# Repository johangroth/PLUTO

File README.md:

#PLUTO --- A WDC65C02 based Single Board Computer ---#

###Links to inspirational projects###

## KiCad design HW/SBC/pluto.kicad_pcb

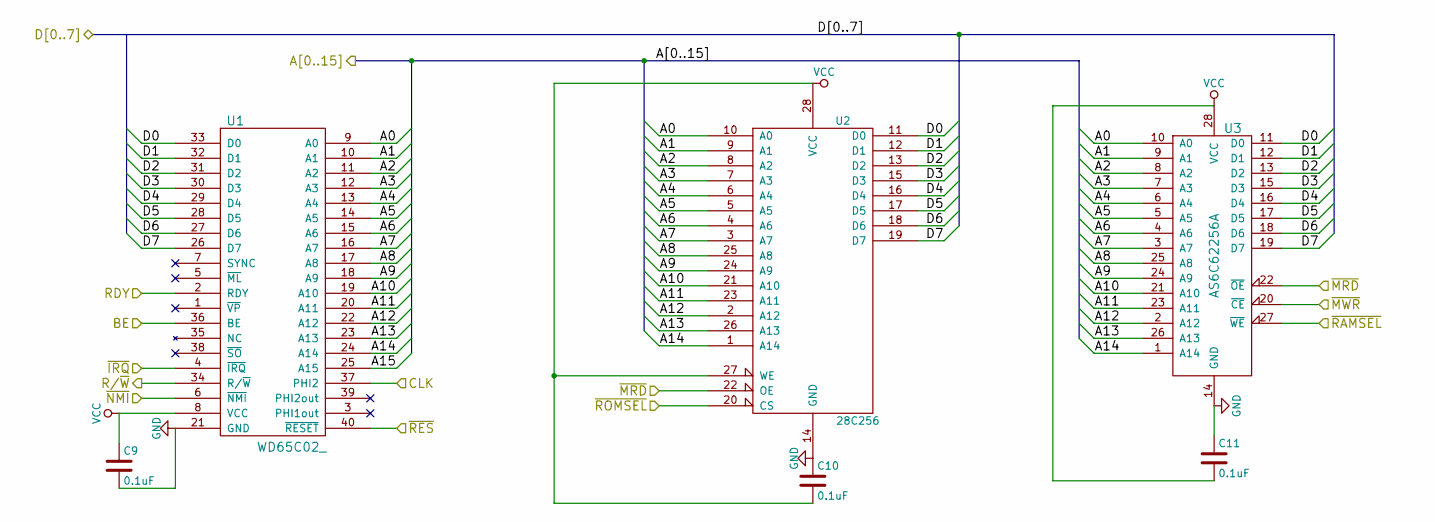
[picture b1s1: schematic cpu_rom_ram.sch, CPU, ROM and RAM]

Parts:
C9, C10, C11: 0.1uF; C_Disc_D3.8mm_W2.6mm_P2.50mm
U1: WD65C02_; DIP-40_W15.24mm_Socket
U2: 28C256; DIP-28_W15.24mm_Socket
U3: AS6C62256A; DIP-28_W15.24mm_Socket

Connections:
/16bit IDE interface/A0: U1.9 (A0), U2.10 (A0), U3.10 (A0); also elsewhere on the board
/16bit IDE interface/A1: U1.10 (A1), U2.9 (A1), U3.9 (A1); also elsewhere on the board
/16bit IDE interface/A2: U1.11 (A2), U2.8 (A2), U3.8 (A2); also elsewhere on the board
/16bit IDE interface/A3: U1.12 (A3), U2.7 (A3), U3.7 (A3); also elsewhere on the board
/16bit IDE interface/CLK: U1.37 (PHI2); also elsewhere on the board
/16bit IDE interface/D0: U1.33 (D0), U2.11 (D0), U3.11 (D0); also elsewhere on the board
/16bit IDE interface/D1: U1.32 (D1), U2.12 (D1), U3.12 (D1); also elsewhere on the board
/16bit IDE interface/D2: U1.31 (D2), U2.13 (D2), U3.13 (D2); also elsewhere on the board
/16bit IDE interface/D3: U1.30 (D3), U2.15 (D3), U3.15 (D3); also elsewhere on the board
/16bit IDE interface/D4: U1.29 (D4), U2.16 (D4), U3.16 (D4); also elsewhere on the board
/16bit IDE interface/D5: U1.28 (D5), U2.17 (D5), U3.17 (D5); also elsewhere on the board
/16bit IDE interface/D6: U1.27 (D6), U2.18 (D6), U3.18 (D6); also elsewhere on the board
/16bit IDE interface/D7: U1.26 (D7), U2.19 (D7), U3.19 (D7); also elsewhere on the board
/16bit IDE interface/~IRQ: U1.4 (~IRQ); also elsewhere on the board
/16bit IDE interface/~MRD: U2.22 (OE), U3.22 (~OE); also elsewhere on the board
/16bit IDE interface/~MWR: U3.20 (~CE); also elsewhere on the board
/16bit IDE interface/~RES: U1.40 (~RESET); also elsewhere on the board
/ACIA and MAX232/R/~W: U1.34 (R/~W); also elsewhere on the board
/Address decoding and support section/A5: U1.14 (A5), U2.5 (A5), U3.5 (A5); also elsewhere on the board
/Address decoding and support section/A6: U1.15 (A6), U2.4 (A6), U3.4 (A6); also elsewhere on the board
/Address decoding and support section/A7: U1.16 (A7), U2.3 (A7), U3.3 (A7); also elsewhere on the board
/Address decoding and support section/A8: U1.17 (A8), U2.25 (A8), U3.25 (A8); also elsewhere on the board
/Address decoding and support section/A9: U1.18 (A9), U2.24 (A9), U3.24 (A9); also elsewhere on the board
/Address decoding and support section/A10: U1.19 (A10), U2.21 (A10), U3.21 (A10); also elsewhere on the board
/Address decoding and support section/A11: U1.20 (A11), U2.23 (A11), U3.23 (A11); also elsewhere on the board
/Address decoding and support section/A12: U1.22 (A12), U2.2 (A12), U3.2 (A12); also elsewhere on the board
/Address decoding and support section/A13: U1.23 (A13), U2.26 (A13), U3.26 (A13); also elsewhere on the board
/Address decoding and support section/A14: U1.24 (A14), U2.1 (A14), U3.1 (A14); also elsewhere on the board
/Address decoding and support section/A15: U1.25 (A15); also elsewhere on the board
/Address decoding and support section/BE: U1.36 (BE); also elsewhere on the board
/Address decoding and support section/RDY: U1.2 (RDY); also elsewhere on the board
/Address decoding and support section/~NMI: U1.6 (~NMI); also elsewhere on the board
/Address decoding and support section/~RAMSEL: U3.27 (~WE); also elsewhere on the board
/Address decoding and support section/~ROMSEL: U2.20 (CS); also elsewhere on the board
/CPU, ROM and RAM/A4: U1.13 (A4), U2.6 (A4), U3.6 (A4); also elsewhere on the board
GND: C9.2, C10.1, C11.1, U1.21 (GND), U2.14 (GND), U3.14 (GND); also elsewhere on the board
VCC: C9.1, C10.2, C11.2, U1.8 (VCC), U2.27 (WE), U2.28 (VCC), U3.28 (VCC); also elsewhere on the board

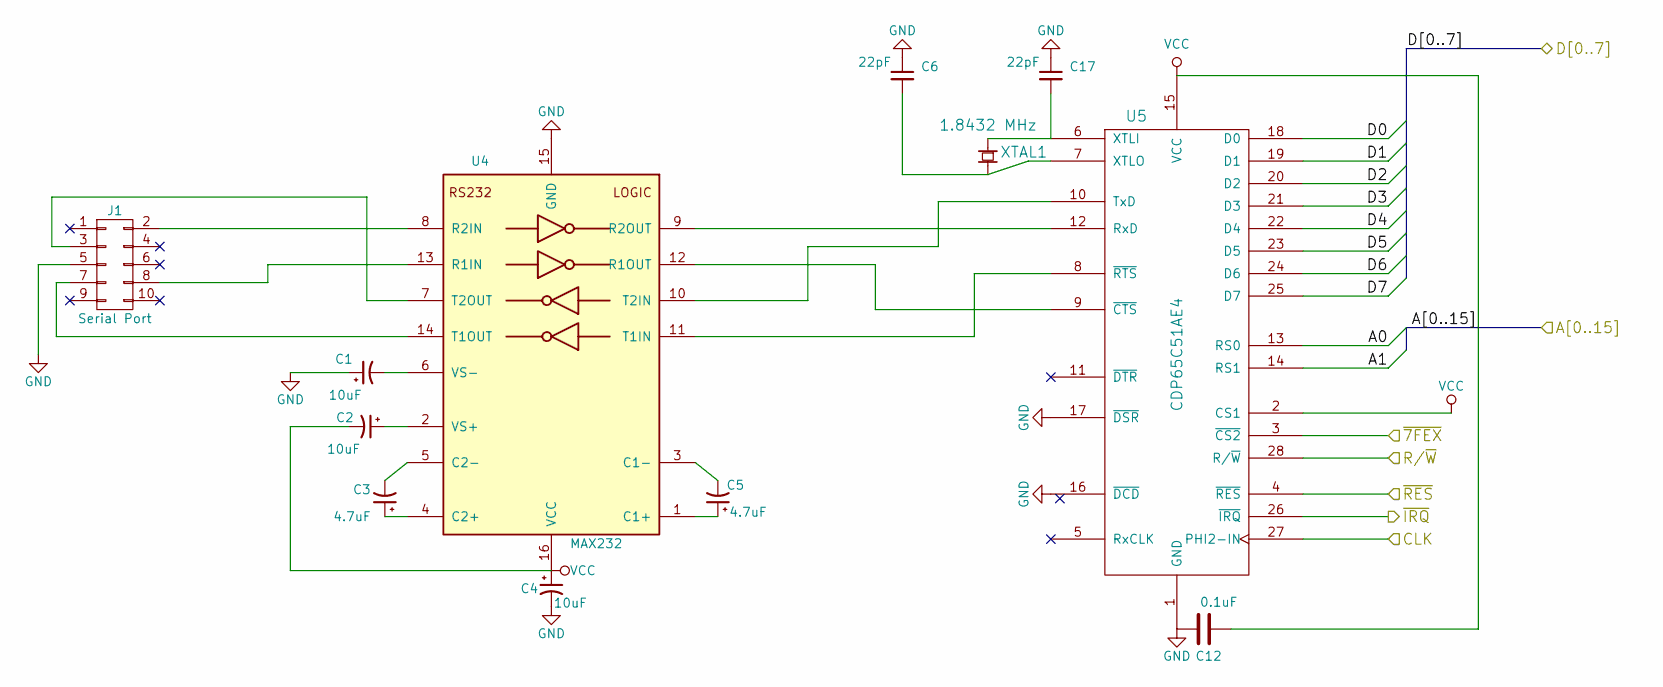
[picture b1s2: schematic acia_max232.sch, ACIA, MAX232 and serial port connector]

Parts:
C1, C2, C4: 10uF; CP_Radial_D5.0mm_P2.50mm
C3, C5: 4.7uF; CP_Radial_D5.0mm_P2.50mm
C6, C17: 22pF; C_Disc_D3.8mm_W2.6mm_P2.50mm
C12: 0.1uF; C_Disc_D3.8mm_W2.6mm_P2.50mm
J1: Serial Port; IDC_Header_Straight_10pins
U4: MAX232; DIP-16_W7.62mm_Socket
U5: CDP65C51AE4; DIP-28_W15.24mm_Socket
XTAL1: 1.8432 MHz; Resonator-2pin_w10.0mm_h5.0mm

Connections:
/16bit IDE interface/A0: U5.13 (RS0); also elsewhere on the board
/16bit IDE interface/A1: U5.14 (RS1); also elsewhere on the board
/16bit IDE interface/CLK: U5.27 (PHI2-IN); also elsewhere on the board
/16bit IDE interface/D0: U5.18 (D0); also elsewhere on the board
/16bit IDE interface/D1: U5.19 (D1); also elsewhere on the board
/16bit IDE interface/D2: U5.20 (D2); also elsewhere on the board
/16bit IDE interface/D3: U5.21 (D3); also elsewhere on the board
/16bit IDE interface/D4: U5.22 (D4); also elsewhere on the board
/16bit IDE interface/D5: U5.23 (D5); also elsewhere on the board
/16bit IDE interface/D6: U5.24 (D6); also elsewhere on the board
/16bit IDE interface/D7: U5.25 (D7); also elsewhere on the board
/16bit IDE interface/~IRQ: U5.26 (~IRQ); also elsewhere on the board
/16bit IDE interface/~RES: U5.4 (~RES); also elsewhere on the board
/ACIA and MAX232/R/~W: U5.28 (R/~W); also elsewhere on the board
/ACIA and MAX232/~7FEX: U5.3 (~CS2); also elsewhere on the board
GND: C1.1, C4.2, C6.1, C12.2, C17.1, J1.5, U4.15 (GND), U5.1 (GND), U5.16 (~DCD), U5.17 (~DSR); also elsewhere on the board
unnamed: C1.2, U4.6 (VS-)
unnamed: C2.1, U4.2 (VS+)
unnamed: C3.1, U4.4 (C2+)
unnamed: C3.2, U4.5 (C2-)
unnamed: C5.1, U4.1 (C1+)
unnamed: C5.2, U4.3 (C1-)
unnamed: C6.2, U5.7 (XTLO), XTAL1.2
unnamed: C17.2, U5.6 (XTLI), XTAL1.1
unnamed: J1.2, U4.8 (R2IN)
unnamed: J1.3, U4.7 (T2OUT)
unnamed: J1.7, U4.14 (T1OUT)
unnamed: J1.8, U4.13 (R1IN)
unnamed: U4.9 (R2OUT), U5.12 (RxD)
unnamed: U4.10 (T2IN), U5.10 (TxD)
unnamed: U4.11 (T1IN), U5.8 (~RTS)
unnamed: U4.12 (R1OUT), U5.9 (~CTS)
VCC: C2.2, C4.1, C12.1, U4.16 (VCC), U5.2 (CS1), U5.15 (VCC); also elsewhere on the board

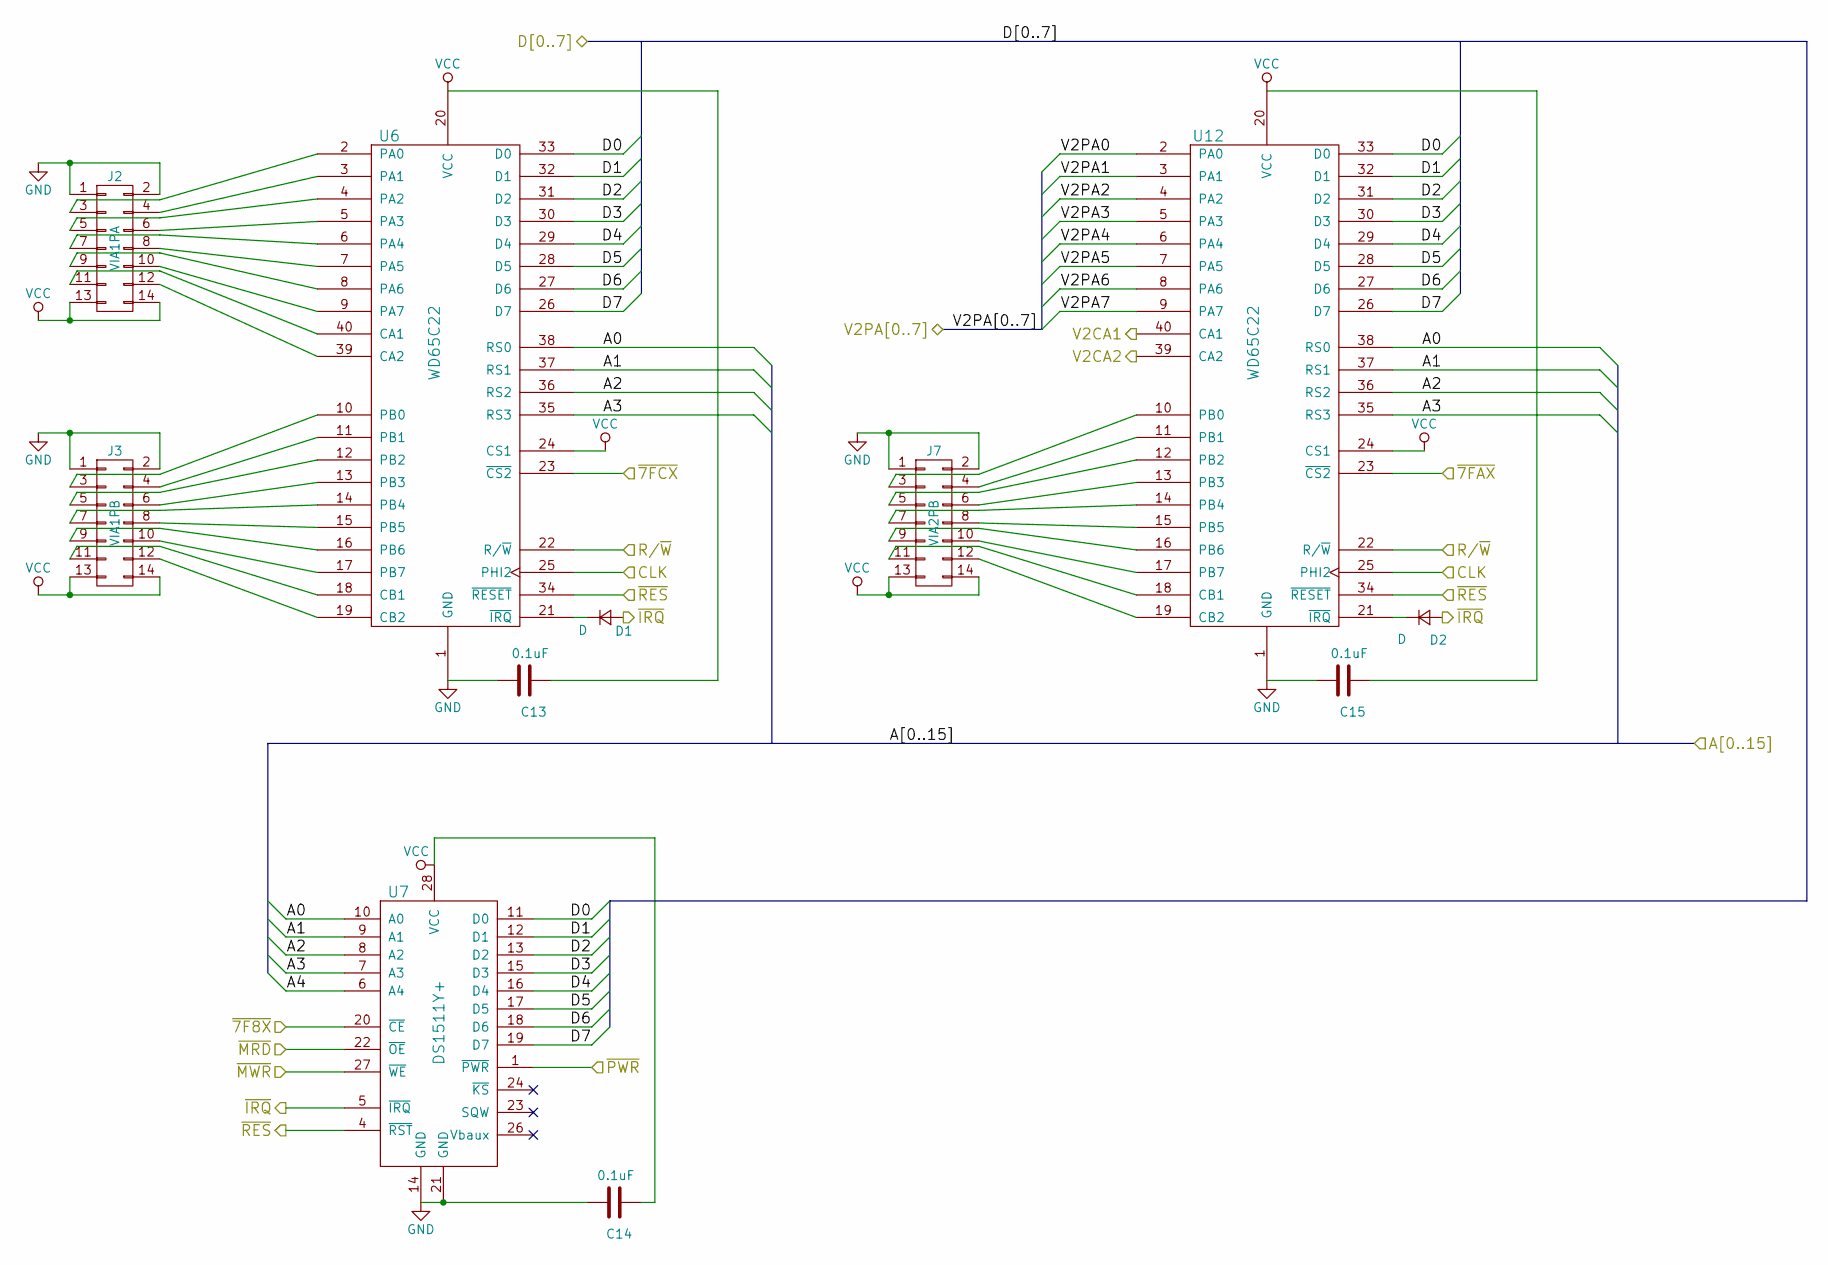
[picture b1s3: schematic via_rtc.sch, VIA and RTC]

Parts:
C13, C14, C15: 0.1uF; C_Disc_D3.8mm_W2.6mm_P2.50mm
D1, D2: D; D_DO-35_SOD27_P7.62mm_Horizontal
J2: VIA1PA; IDC_Header_Straight_14pins
J3: VIA1PB; IDC_Header_Straight_14pins
J7: VIA2PB; IDC_Header_Straight_14pins
U6, U12: WD65C22; DIP-40_W15.24mm_Socket
U7: DS1511Y+; DIP-28_W15.24mm_Socket

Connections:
/16bit IDE interface/A0: U6.38 (RS0), U7.10 (A0), U12.38 (RS0); also elsewhere on the board
/16bit IDE interface/A1: U6.37 (RS1), U7.9 (A1), U12.37 (RS1); also elsewhere on the board
/16bit IDE interface/A2: U6.36 (RS2), U7.8 (A2), U12.36 (RS2); also elsewhere on the board
/16bit IDE interface/A3: U6.35 (RS3), U7.7 (A3), U12.35 (RS3); also elsewhere on the board
/16bit IDE interface/CLK: U6.25 (PHI2), U12.25 (PHI2); also elsewhere on the board
/16bit IDE interface/D0: U6.33 (D0), U7.11 (D0), U12.33 (D0); also elsewhere on the board
/16bit IDE interface/D1: U6.32 (D1), U7.12 (D1), U12.32 (D1); also elsewhere on the board
/16bit IDE interface/D2: U6.31 (D2), U7.13 (D2), U12.31 (D2); also elsewhere on the board
/16bit IDE interface/D3: U6.30 (D3), U7.15 (D3), U12.30 (D3); also elsewhere on the board
/16bit IDE interface/D4: U6.29 (D4), U7.16 (D4), U12.29 (D4); also elsewhere on the board
/16bit IDE interface/D5: U6.28 (D5), U7.17 (D5), U12.28 (D5); also elsewhere on the board
/16bit IDE interface/D6: U6.27 (D6), U7.18 (D6), U12.27 (D6); also elsewhere on the board
/16bit IDE interface/D7: U6.26 (D7), U7.19 (D7), U12.26 (D7); also elsewhere on the board
/16bit IDE interface/~IRQ: D1.2 (A), D2.2 (A), U7.5 (~IRQ); also elsewhere on the board
/16bit IDE interface/~MRD: U7.22 (~OE); also elsewhere on the board
/16bit IDE interface/~MWR: U7.27 (~WE); also elsewhere on the board
/16bit IDE interface/~RES: U6.34 (~RESET), U7.4 (~RST), U12.34 (~RESET); also elsewhere on the board
/ACIA and MAX232/R/~W: U6.22 (R/~W), U12.22 (R/~W); also elsewhere on the board
/Address decoding and support section/~7F8X: U7.20 (~CE); also elsewhere on the board
/Address decoding and support section/~7FAX: U12.23 (~CS2); also elsewhere on the board
/Address decoding and support section/~7FCX: U6.23 (~CS2); also elsewhere on the board
/Address decoding and support section/~PWR: U7.1 (~PWR); also elsewhere on the board
/Audio/V2CA1: U12.40 (CA1); also elsewhere on the board
/Audio/V2CA2: U12.39 (CA2); also elsewhere on the board
/Audio/V2PA0: U12.2 (PA0); also elsewhere on the board
/Audio/V2PA1: U12.3 (PA1); also elsewhere on the board
/Audio/V2PA2: U12.4 (PA2); also elsewhere on the board
/Audio/V2PA3: U12.5 (PA3); also elsewhere on the board
/Audio/V2PA4: U12.6 (PA4); also elsewhere on the board
/Audio/V2PA5: U12.7 (PA5); also elsewhere on the board
/Audio/V2PA6: U12.8 (PA6); also elsewhere on the board
/Audio/V2PA7: U12.9 (PA7); also elsewhere on the board
/CPU, ROM and RAM/A4: U7.6 (A4); also elsewhere on the board
GND: C13.2, C14.2, C15.2, J2.1, J2.2, J3.1, J3.2, J7.1, J7.2, U6.1 (GND), U7.14 (GND), U7.21 (GND), U12.1 (GND); also elsewhere on the board
unnamed: D1.1 (K), U6.21 (~IRQ)
unnamed: D2.1 (K), U12.21 (~IRQ)
unnamed: J2.3, U6.2 (PA0)
unnamed: J2.4, U6.3 (PA1)
unnamed: J2.5, U6.4 (PA2)
unnamed: J2.6, U6.5 (PA3)
unnamed: J2.7, U6.6 (PA4)
unnamed: J2.8, U6.7 (PA5)
unnamed: J2.9, U6.8 (PA6)
unnamed: J2.10, U6.9 (PA7)
unnamed: J2.11, U6.40 (CA1)
unnamed: J2.12, U6.39 (CA2)
unnamed: J3.3, U6.10 (PB0)
unnamed: J3.4, U6.11 (PB1)
unnamed: J3.5, U6.12 (PB2)
unnamed: J3.6, U6.13 (PB3)
unnamed: J3.7, U6.14 (PB4)
unnamed: J3.8, U6.15 (PB5)
unnamed: J3.9, U6.16 (PB6)
unnamed: J3.10, U6.17 (PB7)
unnamed: J3.11, U6.18 (CB1)
unnamed: J3.12, U6.19 (CB2)
unnamed: J7.3, U12.10 (PB0)
unnamed: J7.4, U12.11 (PB1)
unnamed: J7.5, U12.12 (PB2)
unnamed: J7.6, U12.13 (PB3)
unnamed: J7.7, U12.14 (PB4)
unnamed: J7.8, U12.15 (PB5)
unnamed: J7.9, U12.16 (PB6)
unnamed: J7.10, U12.17 (PB7)
unnamed: J7.11, U12.18 (CB1)
unnamed: J7.12, U12.19 (CB2)
VCC: C13.1, C14.1, C15.1, J2.13, J2.14, J3.13, J3.14, J7.13, J7.14, U6.20 (VCC), U6.24 (CS1), U7.28 (VCC), U12.20 (VCC), U12.24 (CS1); also elsewhere on the board

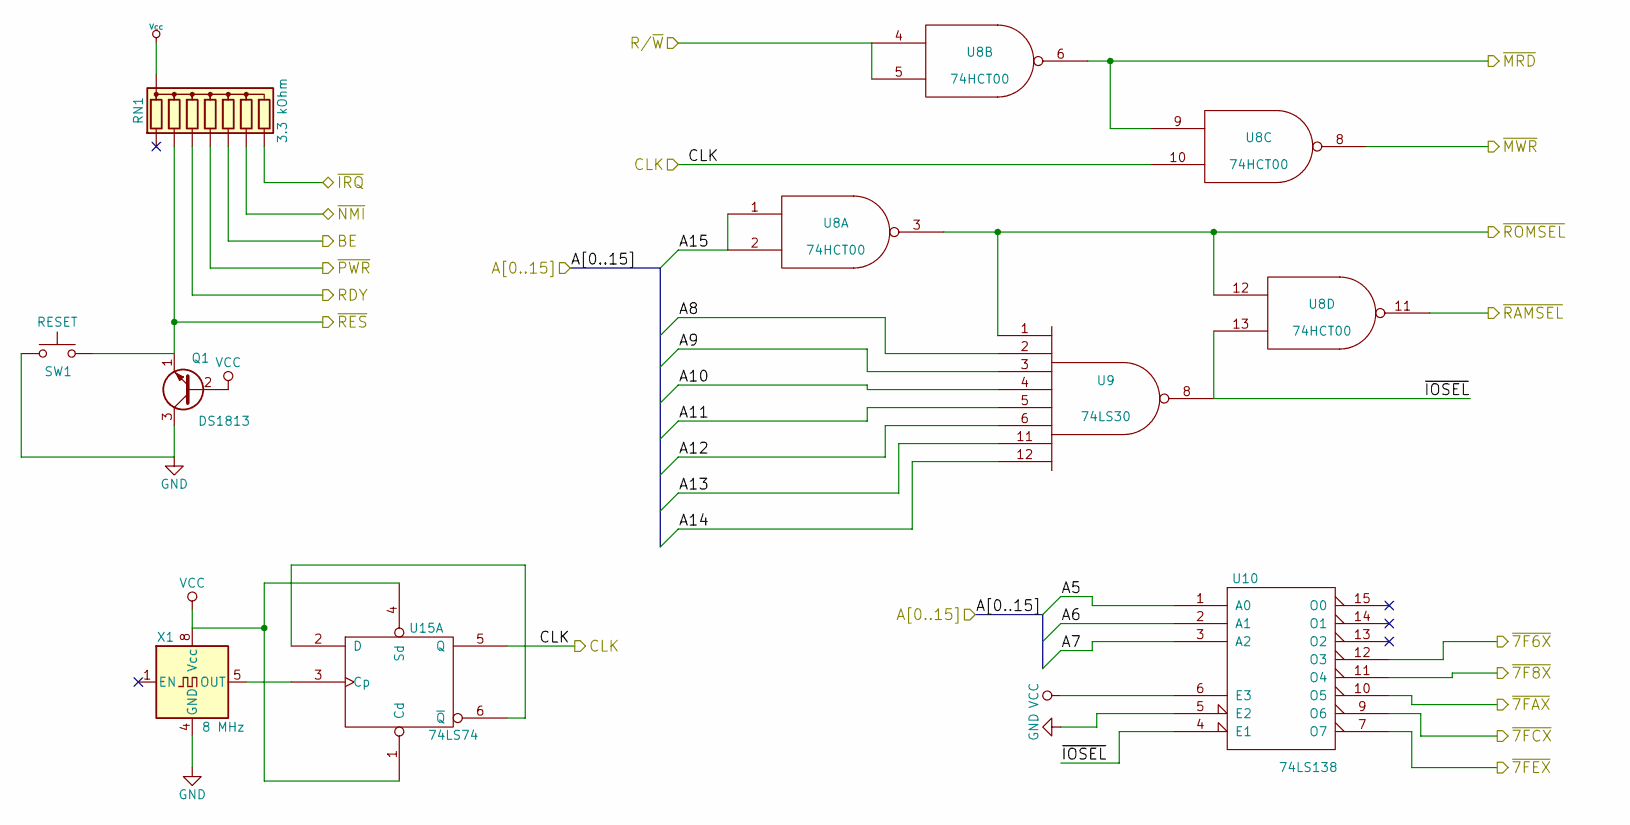
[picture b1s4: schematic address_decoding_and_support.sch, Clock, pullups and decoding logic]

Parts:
Q1: DS1813; TO-92_Inline_Narrow_Oval
RN1: 3.3 kOhm; Pin_Header_Straight_1x08_Pitch2.54mm
SW1: RESET; SW_PUSH_6mm_h4.3mm
U8: 74HCT00; DIP-14_W7.62mm_Socket
U9: 74LS30; DIP-14_W7.62mm_Socket
U10: 74LS138; DIP-16_W7.62mm_Socket
U15: 74LS74; DIP-14_W7.62mm_Socket
X1: 8 MHz; DIP-8_W7.62mm_Socket

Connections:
/16bit IDE interface/CLK: U8.10, U15.5 (Q); also elsewhere on the board
/16bit IDE interface/~7F6X: U10.12 (O3); also elsewhere on the board
/16bit IDE interface/~IRQ: RN1.8 (R7); also elsewhere on the board
/16bit IDE interface/~MRD: U8.6, U8.9; also elsewhere on the board
/16bit IDE interface/~MWR: U8.8; also elsewhere on the board
/16bit IDE interface/~RES: Q1.1 (E), RN1.3 (R2), SW1.2; also elsewhere on the board
/ACIA and MAX232/R/~W: U8.4, U8.5; also elsewhere on the board
/ACIA and MAX232/~7FEX: U10.7 (O7); also elsewhere on the board
/Address decoding and support section/A5: U10.1 (A0); also elsewhere on the board
/Address decoding and support section/A6: U10.2 (A1); also elsewhere on the board
/Address decoding and support section/A7: U10.3 (A2); also elsewhere on the board
/Address decoding and support section/A8: U9.2; also elsewhere on the board
/Address decoding and support section/A9: U9.3; also elsewhere on the board
/Address decoding and support section/A10: U9.4; also elsewhere on the board
/Address decoding and support section/A11: U9.5; also elsewhere on the board
/Address decoding and support section/A12: U9.6; also elsewhere on the board
/Address decoding and support section/A13: U9.11; also elsewhere on the board
/Address decoding and support section/A14: U9.12; also elsewhere on the board
/Address decoding and support section/A15: U8.1, U8.2; also elsewhere on the board
/Address decoding and support section/BE: RN1.6 (R5); also elsewhere on the board
/Address decoding and support section/RDY: RN1.4 (R3); also elsewhere on the board
/Address decoding and support section/~7F8X: U10.11 (O4); also elsewhere on the board
/Address decoding and support section/~7FAX: U10.10 (O5); also elsewhere on the board
/Address decoding and support section/~7FCX: U10.9 (O6); also elsewhere on the board
/Address decoding and support section/~IOSEL: U8.13, U9.8, U10.4 (E1)
/Address decoding and support section/~NMI: RN1.7 (R6); also elsewhere on the board
/Address decoding and support section/~PWR: RN1.5 (R4); also elsewhere on the board
/Address decoding and support section/~RAMSEL: U8.11; also elsewhere on the board
/Address decoding and support section/~ROMSEL: U8.3, U8.12, U9.1; also elsewhere on the board
GND: Q1.3 (C), SW1.1, U8.7 (GND), U9.7 (GND), U10.5 (E2), U10.8 (GND), U15.7 (GND), X1.4 (GND); also elsewhere on the board
unnamed: U15.2 (D), U15.6 (~Q)
unnamed: U15.3 (Cp), X1.5 (OUT)
VCC: Q1.2 (B), RN1.1 (common), U8.14 (VCC), U9.14 (VCC), U10.6 (E3), U10.16 (VCC), U15.1 (Cd), U15.4 (Sd), U15.14 (VCC), X1.8 (Vcc); also elsewhere on the board

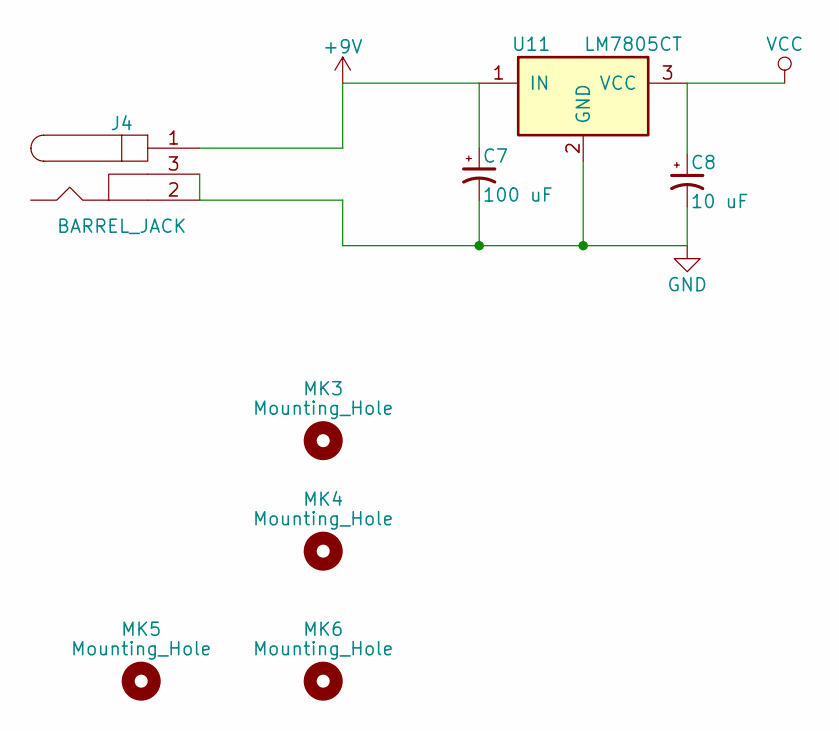
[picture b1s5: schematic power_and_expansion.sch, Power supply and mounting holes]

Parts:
C7: 100 uF; CP_Radial_D6.3mm_P2.50mm
C8: 10 uF; CP_Radial_D5.0mm_P2.00mm
J4: BARREL_JACK
MK3, MK4, MK5, MK6: Mounting_Hole; MountingHole_3.2mm_M3_Pad
U11: LM7805CT; TO-220_Vertical

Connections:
+9V: C7.1, J4.1, U11.1 (IN)
GND: C7.2, C8.2, J4.2, J4.3, U11.2 (GND); also elsewhere on the board
VCC: C8.1, U11.3 (VCC); also elsewhere on the board

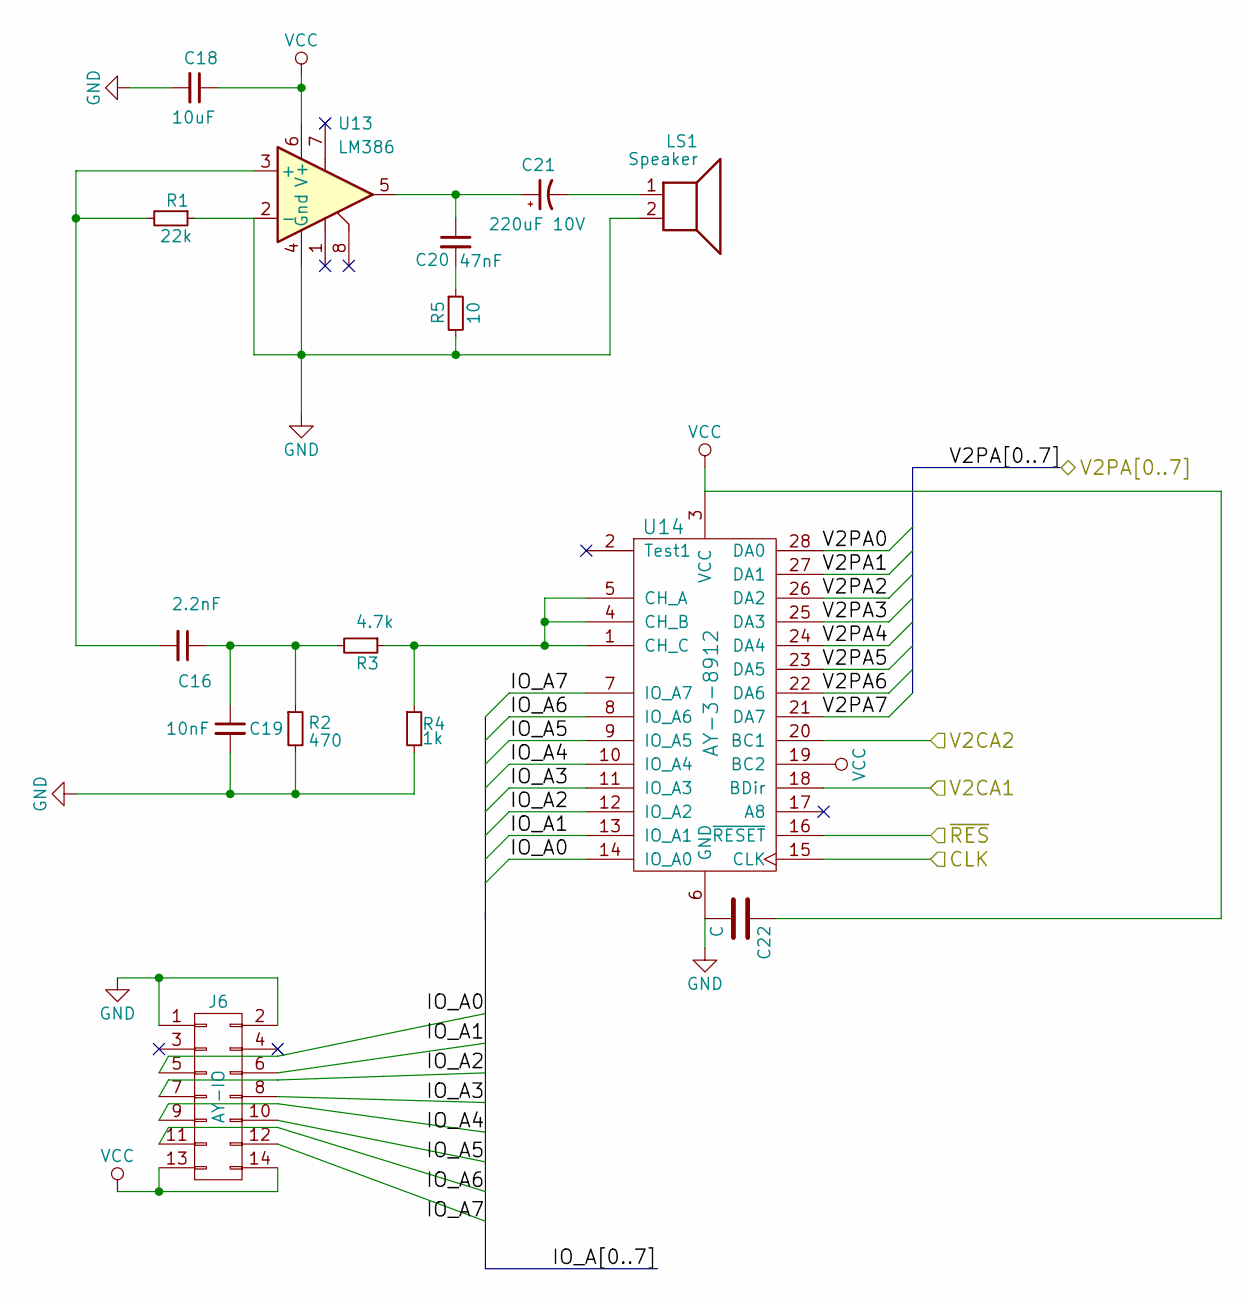
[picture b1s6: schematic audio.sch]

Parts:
C16: 2.2nF; C_Disc_D3.8mm_W2.6mm_P2.50mm
C18: 10uF; C_Disc_D3.8mm_W2.6mm_P2.50mm
C19: 10nF; C_Disc_D3.8mm_W2.6mm_P2.50mm
C20: 47nF; C_Disc_D3.8mm_W2.6mm_P2.50mm
C21: 220uF 10V; CP_Radial_D6.3mm_P2.50mm
C22: C; C_Disc_D3.8mm_W2.6mm_P2.50mm
J6: AY-IO; IDC_Header_Straight_14pins
LS1: Speaker; PJ311_3.5mm_Jack
R1: 22k; R_Axial_DIN0411_L9.9mm_D3.6mm_P12.70mm_Horizontal
R2: 470; R_Axial_DIN0411_L9.9mm_D3.6mm_P12.70mm_Horizontal
R3: 4.7k; R_Axial_DIN0411_L9.9mm_D3.6mm_P12.70mm_Horizontal
R4: 1k; R_Axial_DIN0411_L9.9mm_D3.6mm_P12.70mm_Horizontal
R5: 10; R_Axial_DIN0411_L9.9mm_D3.6mm_P12.70mm_Horizontal
U13: LM386; DIP-8_W7.62mm_Socket
U14: AY-3-8912; DIP-28_W15.24mm_Socket

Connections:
/16bit IDE interface/CLK: U14.15 (CLK); also elsewhere on the board
/16bit IDE interface/~RES: U14.16 (~RESET); also elsewhere on the board
/Audio/IO_A0: J6.5, U14.14 (IO_A0)
/Audio/IO_A1: J6.6, U14.13 (IO_A1)
/Audio/IO_A2: J6.7, U14.12 (IO_A2)
/Audio/IO_A3: J6.8, U14.11 (IO_A3)
/Audio/IO_A4: J6.9, U14.10 (IO_A4)
/Audio/IO_A5: J6.10, U14.9 (IO_A5)
/Audio/IO_A6: J6.11, U14.8 (IO_A6)
/Audio/IO_A7: J6.12, U14.7 (IO_A7)
/Audio/V2CA1: U14.18 (BDir); also elsewhere on the board
/Audio/V2CA2: U14.20 (BC1); also elsewhere on the board
/Audio/V2PA0: U14.28 (DA0); also elsewhere on the board
/Audio/V2PA1: U14.27 (DA1); also elsewhere on the board
/Audio/V2PA2: U14.26 (DA2); also elsewhere on the board
/Audio/V2PA3: U14.25 (DA3); also elsewhere on the board
/Audio/V2PA4: U14.24 (DA4); also elsewhere on the board
/Audio/V2PA5: U14.23 (DA5); also elsewhere on the board
/Audio/V2PA6: U14.22 (DA6); also elsewhere on the board
/Audio/V2PA7: U14.21 (DA7); also elsewhere on the board
GND: C18.2, C19.2, C22.2, J6.1, J6.2, LS1.2, R1.1, R2.2, R4.2, R5.2, U13.2 (-), U13.4 (Gnd), U14.6 (GND); also elsewhere on the board
unnamed: C16.1, C19.1, R2.1, R3.2
unnamed: C16.2, R1.2, U13.3 (+)
unnamed: C20.1, C21.1, U13.5
unnamed: C20.2, R5.1
unnamed: C21.2, LS1.1
unnamed: R3.1, R4.1, U14.1 (CH_C), U14.4 (CH_B), U14.5 (CH_A)
VCC: C18.1, C22.1, J6.13, J6.14, U13.6 (V+), U14.3 (VCC), U14.19 (BC2); also elsewhere on the board

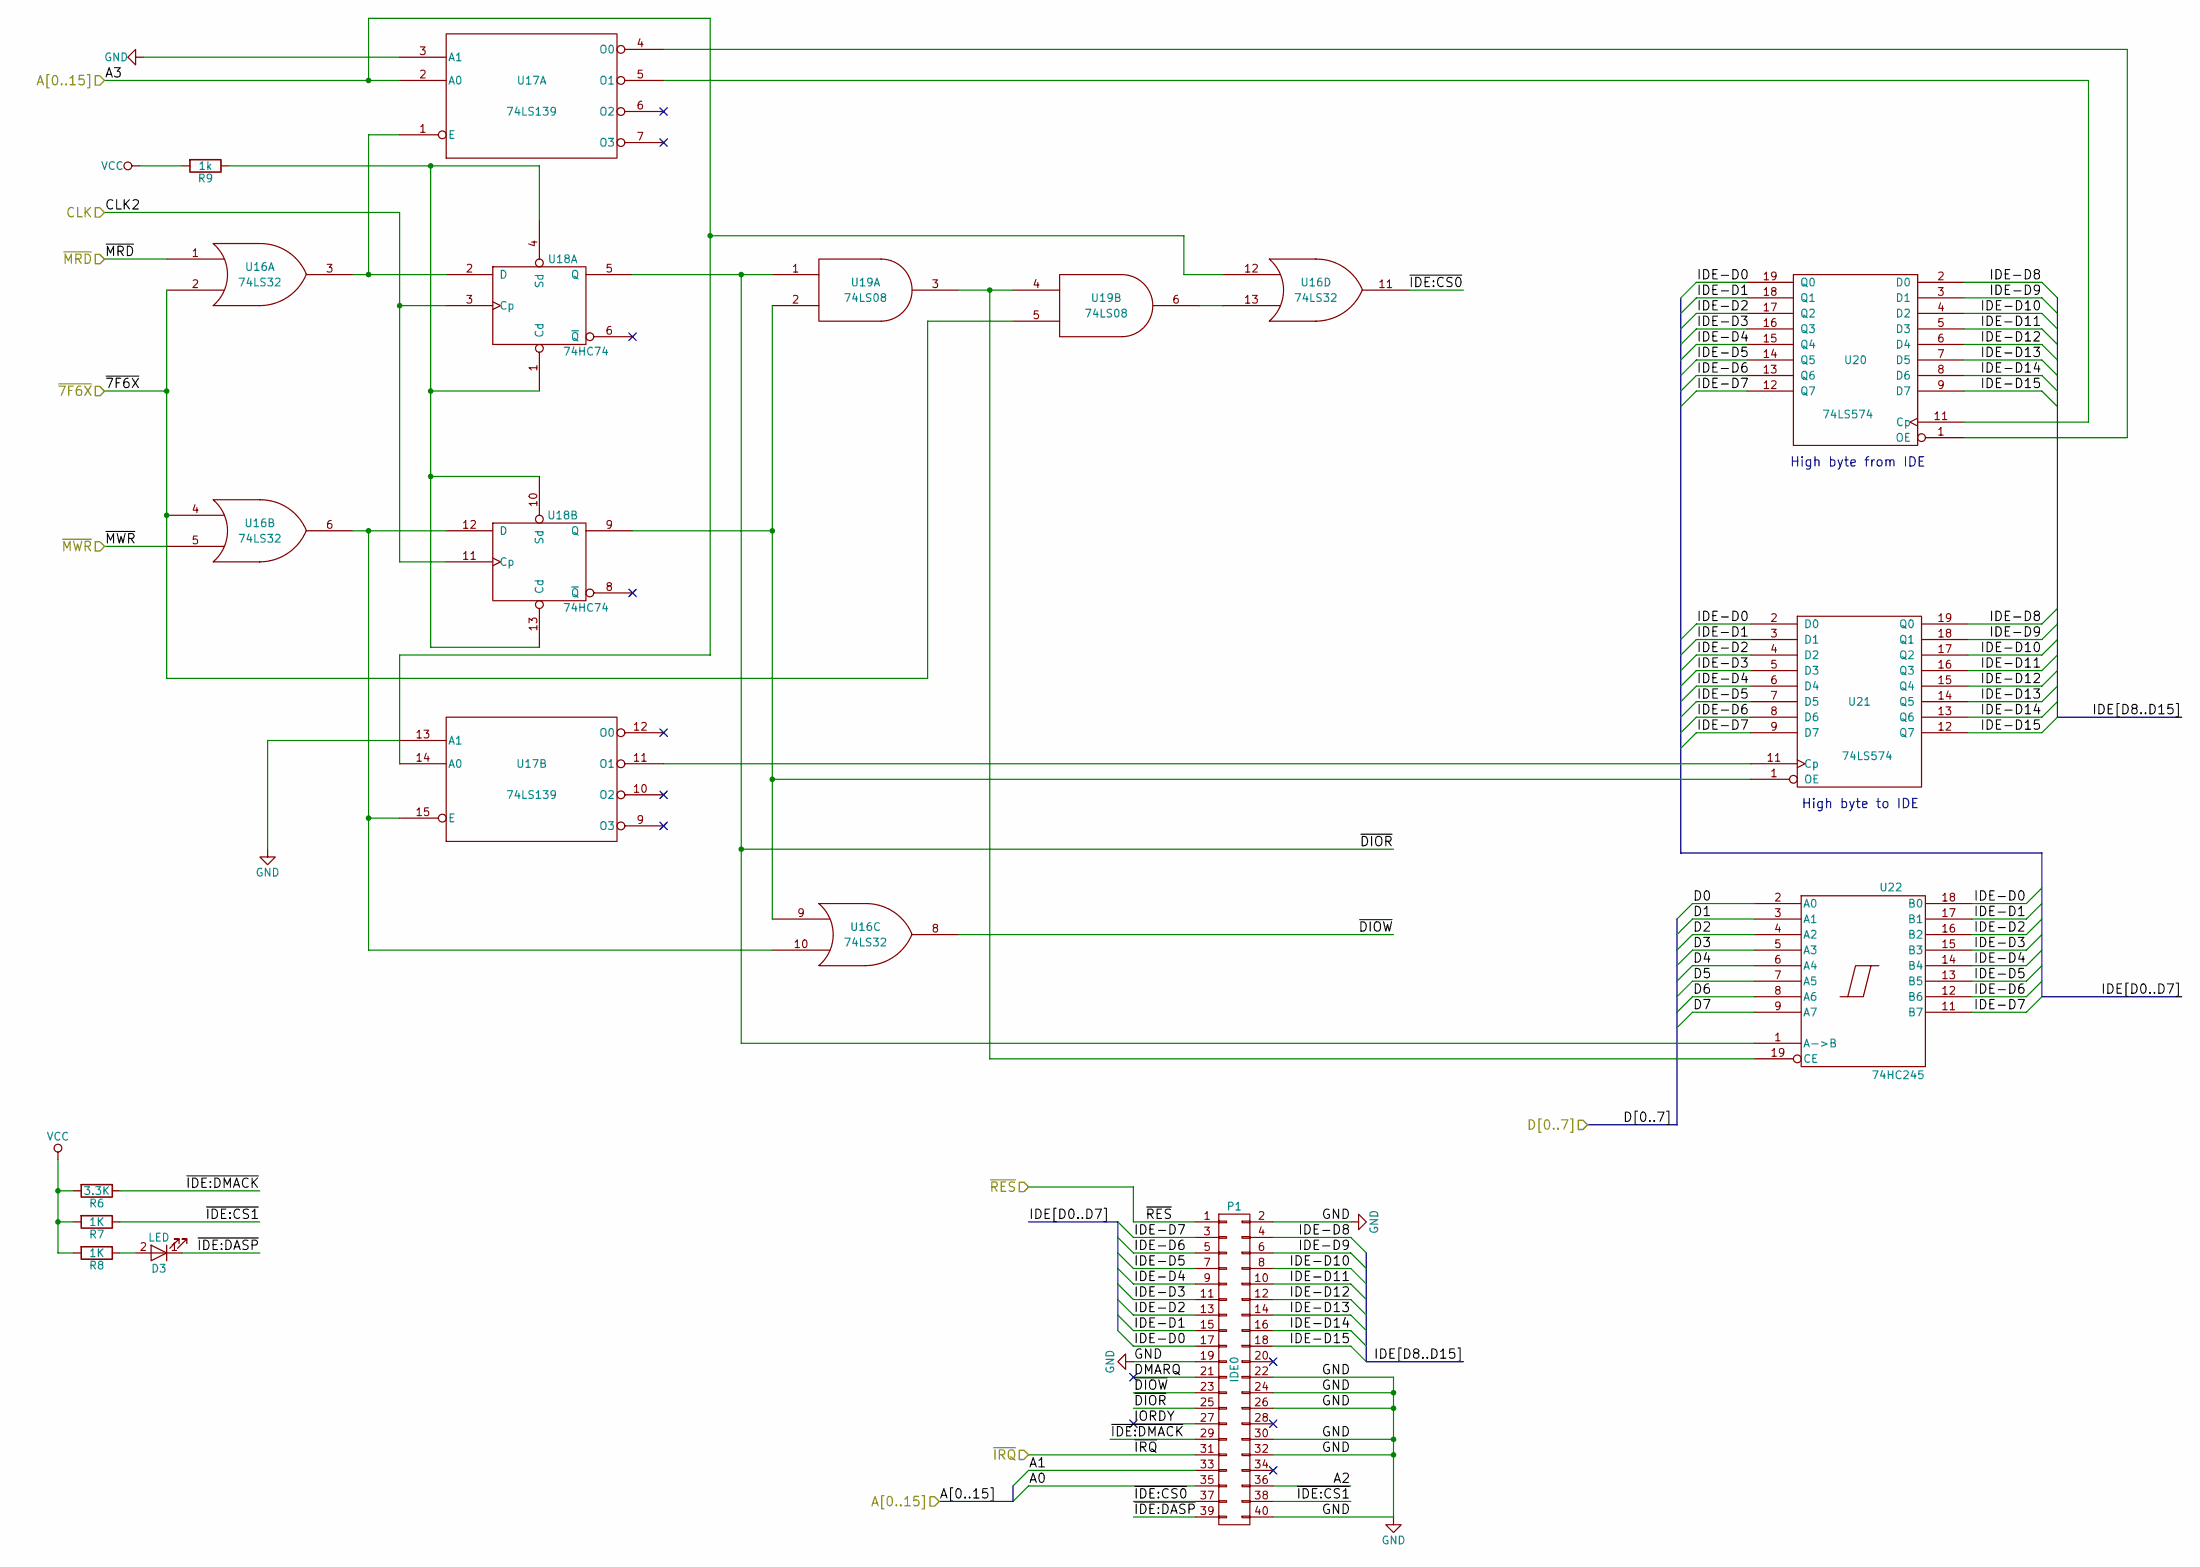
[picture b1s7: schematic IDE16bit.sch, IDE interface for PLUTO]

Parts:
D3: LED; LED_D3.0mm
P1: IDE0; IDC_Header_Straight_40pins
R6: 3.3K; R_Axial_DIN0411_L9.9mm_D3.6mm_P12.70mm_Horizontal
R7, R8: 1K; R_Axial_DIN0411_L9.9mm_D3.6mm_P12.70mm_Horizontal
R9: 1k; R_Axial_DIN0411_L9.9mm_D3.6mm_P12.70mm_Horizontal
U16: 74LS32; DIP-14_W7.62mm_Socket
U17: 74LS139; DIP-16_W7.62mm_Socket
U18: 74HC74; DIP-14_W7.62mm_Socket
U19: 74LS08; DIP-14_W7.62mm_Socket
U20, U21: 74LS574; DIP-20_W7.62mm_Socket
U22: 74HC245; DIP-20_W7.62mm_Socket

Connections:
/16bit IDE interface/A0: P1.35; also elsewhere on the board
/16bit IDE interface/A1: P1.33; also elsewhere on the board
/16bit IDE interface/A2: P1.36; also elsewhere on the board
/16bit IDE interface/A3: U16.12, U17.2 (A0), U17.14 (A0); also elsewhere on the board
/16bit IDE interface/CLK: U18.3 (Cp), U18.11 (Cp); also elsewhere on the board
/16bit IDE interface/D0: U22.2 (A0); also elsewhere on the board
/16bit IDE interface/D1: U22.3 (A1); also elsewhere on the board
/16bit IDE interface/D2: U22.4 (A2); also elsewhere on the board
/16bit IDE interface/D3: U22.5 (A3); also elsewhere on the board
/16bit IDE interface/D4: U22.6 (A4); also elsewhere on the board
/16bit IDE interface/D5: U22.7 (A5); also elsewhere on the board
/16bit IDE interface/D6: U22.8 (A6); also elsewhere on the board
/16bit IDE interface/D7: U22.9 (A7); also elsewhere on the board
/16bit IDE interface/IDE-D0: P1.17, U20.19 (Q0), U21.2 (D0), U22.18 (B0)
/16bit IDE interface/IDE-D1: P1.15, U20.18 (Q1), U21.3 (D1), U22.17 (B1)
/16bit IDE interface/IDE-D2: P1.13, U20.17 (Q2), U21.4 (D2), U22.16 (B2)
/16bit IDE interface/IDE-D3: P1.11, U20.16 (Q3), U21.5 (D3), U22.15 (B3)
/16bit IDE interface/IDE-D4: P1.9, U20.15 (Q4), U21.6 (D4), U22.14 (B4)
/16bit IDE interface/IDE-D5: P1.7, U20.14 (Q5), U21.7 (D5), U22.13 (B5)
/16bit IDE interface/IDE-D6: P1.5, U20.13 (Q6), U21.8 (D6), U22.12 (B6)
/16bit IDE interface/IDE-D7: P1.3, U20.12 (Q7), U21.9 (D7), U22.11 (B7)
/16bit IDE interface/IDE-D8: P1.4, U20.2 (D0), U21.19 (Q0)
/16bit IDE interface/IDE-D9: P1.6, U20.3 (D1), U21.18 (Q1)
/16bit IDE interface/IDE-D10: P1.8, U20.4 (D2), U21.17 (Q2)
/16bit IDE interface/IDE-D11: P1.10, U20.5 (D3), U21.16 (Q3)
/16bit IDE interface/IDE-D12: P1.12, U20.6 (D4), U21.15 (Q4)
/16bit IDE interface/IDE-D13: P1.14, U20.7 (D5), U21.14 (Q5)
/16bit IDE interface/IDE-D14: P1.16, U20.8 (D6), U21.13 (Q6)
/16bit IDE interface/IDE-D15: P1.18, U20.9 (D7), U21.12 (Q7)
/16bit IDE interface/~7F6X: U16.2, U16.4, U19.5; also elsewhere on the board
/16bit IDE interface/~DIOR: P1.25, U18.5 (Q), U19.1, U22.1 (A->B)
/16bit IDE interface/~DIOW: P1.23, U16.8
/16bit IDE interface/~IDE:CS0: P1.37, U16.11
/16bit IDE interface/~IDE:CS1: P1.38, R7.1
/16bit IDE interface/~IDE:DASP: D3.1 (K), P1.39
/16bit IDE interface/~IDE:DMACK: P1.29, R6.1
/16bit IDE interface/~IRQ: P1.31; also elsewhere on the board
/16bit IDE interface/~MRD: U16.1; also elsewhere on the board
/16bit IDE interface/~MWR: U16.5; also elsewhere on the board
/16bit IDE interface/~RES: P1.1; also elsewhere on the board
GND: P1.2, P1.19, P1.22, P1.24, P1.26, P1.30, P1.32, P1.40, U16.7 (GND), U17.3 (A1), U17.8 (GND), U17.13 (A1), U18.7 (GND), U19.7 (GND), U20.10 (GND), U21.10 (GND), U22.10 (GND); also elsewhere on the board
unnamed: D3.2 (A), R8.1
unnamed: R9.1, U18.1 (Cd), U18.4 (Sd), U18.10 (Sd), U18.13 (Cd)
unnamed: U16.3, U17.1 (E), U18.2 (D)
unnamed: U16.9, U18.9 (Q), U19.2, U21.1 (OE)
unnamed: U16.6, U16.10, U17.15 (E), U18.12 (D)
unnamed: U16.13, U19.6
unnamed: U17.4 (O0), U20.1 (OE)
unnamed: U17.5 (O1), U20.11 (Cp)
unnamed: U17.11 (O1), U21.11 (Cp)
unnamed: U19.3, U19.4, U22.19 (CE)
VCC: R6.2, R7.2, R8.2, R9.2, U16.14 (VCC), U17.16 (VCC), U18.14 (VCC), U19.14 (VCC), U20.20 (VCC), U21.20 (VCC), U22.20 (VCC); also elsewhere on the board

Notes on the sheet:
High byte from IDE
High byte to IDE
